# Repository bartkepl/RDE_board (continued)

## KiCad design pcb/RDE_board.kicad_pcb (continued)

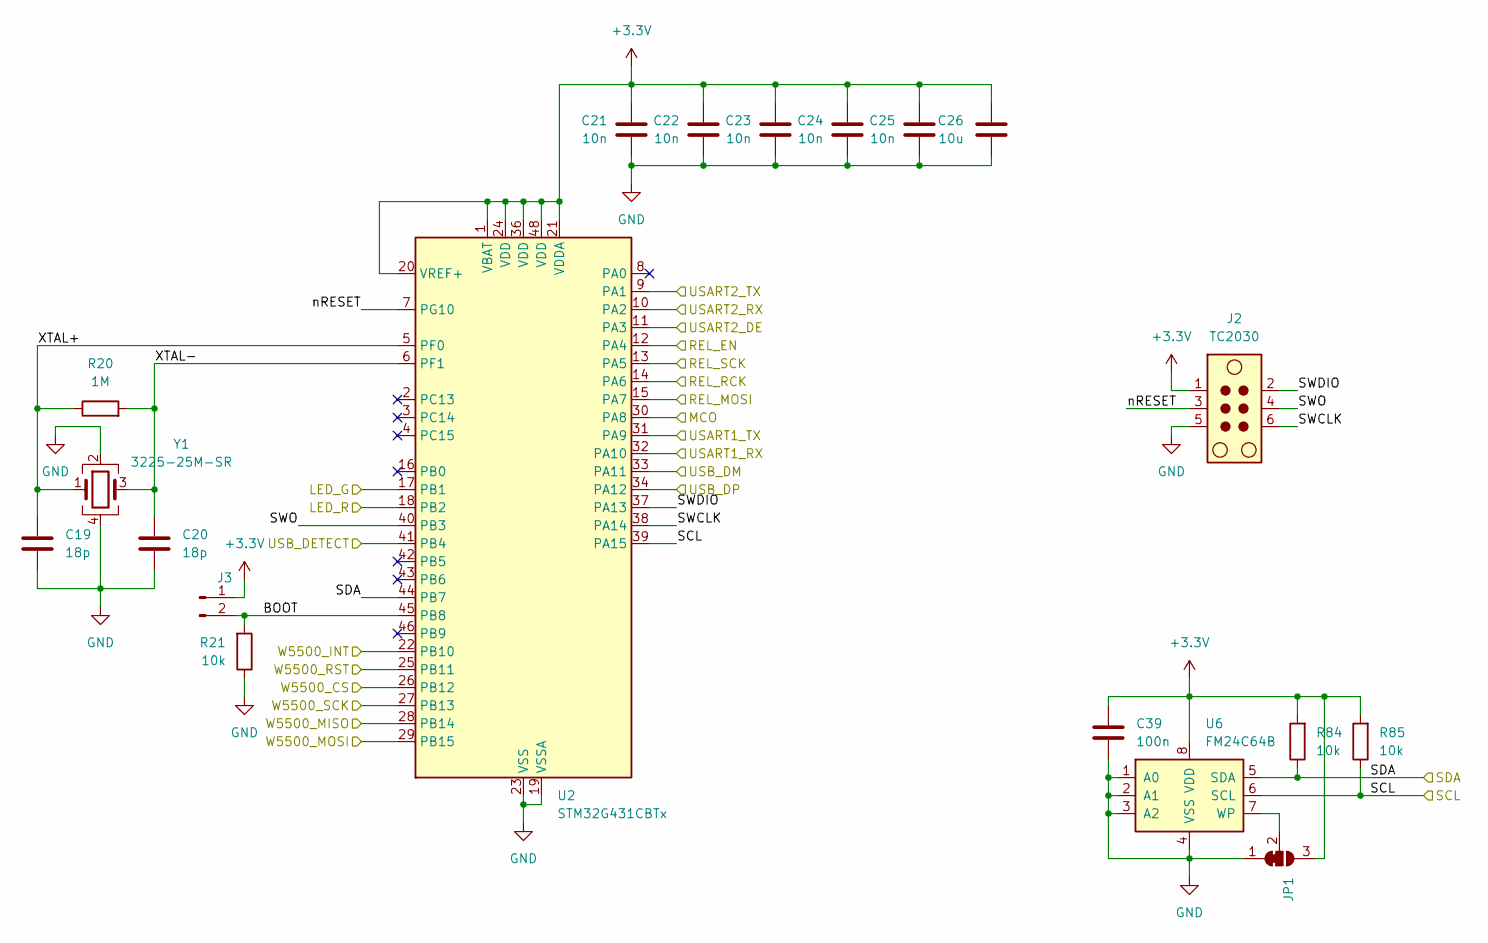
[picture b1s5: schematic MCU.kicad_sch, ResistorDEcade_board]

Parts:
C19, C20: 18p; C_0402_1005Metric_Pad0.74x0.62mm_HandSolder
C21, C22, C23, C24, C25: 10n; C_0603_1608Metric_Pad1.08x0.95mm_HandSolder
C26: 10u; C_1206_3216Metric_Pad1.33x1.80mm_HandSolder
C39: 100n; C_0603_1608Metric_Pad1.08x0.95mm_HandSolder
J2: TC2030; Tag-Connect_TC2030-IDC-NL_2x03_P1.27mm_Vertical
J3: Conn_01x02_Pin; PinHeader_1x02_P2.00mm_Vertical
JP1: SolderJumper_3_Bridged12; SolderJumper-3_P1.3mm_Bridged12_Pad1.0x1.5mm
R20: 1M; R_0402_1005Metric_Pad0.72x0.64mm_HandSolder
R21, R84, R85: 10k; R_0603_1608Metric_Pad0.98x0.95mm_HandSolder
U2: STM32G431CBTx; LQFP-48_7x7mm_P0.5mm
U6: FM24C64B; SOIC-8_3.9x4.9mm_P1.27mm
Y1: 3225-25M-SR; Crystal_SMD_3225-4Pin_3.2x2.5mm

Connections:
+3.3V: C21.2, C22.2, C23.2, C24.2, C25.2, C26.1, C39.1, J2.1, J3.1, JP1.3 (B), R84.2, R85.2, U2.1 (VBAT), U2.20 (VREF+), U2.21 (VDDA), U2.24 (VDD), U2.36 (VDD), U2.48 (VDD), U6.8 (VDD); also elsewhere on the board
/ConnectorDIN41612/DE: U2.11 (PA3); also elsewhere on the board
/ConnectorDIN41612/RxD: U2.10 (PA2); also elsewhere on the board
/ConnectorDIN41612/TxD: U2.9 (PA1); also elsewhere on the board
/ConnectorDIN41612/USART+: U2.31 (PA9); also elsewhere on the board
/ConnectorDIN41612/USART-: U2.32 (PA10); also elsewhere on the board
/ConnectorDIN41612/USB_D+: U2.34 (PA12); also elsewhere on the board
/ConnectorDIN41612/USB_D-: U2.33 (PA11); also elsewhere on the board
/ConnectorDIN41612/USB_DET: U2.41 (PB4); also elsewhere on the board
/EthernetPHY/CLKIN: U2.30 (PA8); also elsewhere on the board
/EthernetPHY/CS: U2.26 (PB12); also elsewhere on the board
/EthernetPHY/INT: U2.22 (PB10); also elsewhere on the board
/EthernetPHY/MISO: U2.28 (PB14); also elsewhere on the board
/EthernetPHY/MOSI: U2.29 (PB15); also elsewhere on the board
/EthernetPHY/RST: U2.25 (PB11); also elsewhere on the board
/EthernetPHY/SCK: U2.27 (PB13); also elsewhere on the board
/Frontend/RCK: U2.14 (PA6); also elsewhere on the board
/Frontend/REL_EN: U2.12 (PA4); also elsewhere on the board
/Frontend/SER_IN: U2.15 (PA7); also elsewhere on the board
/Frontend/SRCK: U2.13 (PA5); also elsewhere on the board
/MCU/BOOT: J3.2, R21.2, U2.45 (PB8)
/MCU/LED_G: U2.17 (PB1); also elsewhere on the board
/MCU/LED_R: U2.18 (PB2); also elsewhere on the board
/MCU/SCL: R85.1, U2.39 (PA15), U6.6 (SCL); also elsewhere on the board
/MCU/SDA: R84.1, U2.44 (PB7), U6.5 (SDA); also elsewhere on the board
/MCU/SWCLK: J2.6, U2.38 (PA14)
/MCU/SWDIO: J2.2, U2.37 (PA13)
/MCU/SWO: J2.4, U2.40 (PB3)
/MCU/XTAL+: C19.1, R20.1, U2.5 (PF0), Y1.1
/MCU/XTAL-: C20.1, R20.2, U2.6 (PF1), Y1.3
/MCU/nRESET: J2.3, U2.7 (PG10)
GND: C19.2, C20.2, C21.1, C22.1, C23.1, C24.1, C25.1, C26.2, C39.2, J2.5, JP1.1 (A), R21.1, U2.19 (VSSA), U2.23 (VSS), U2.35 (VSS), U2.47 (VSS), U6.1 (A0), U6.2 (A1), U6.3 (A2), U6.4 (VSS), Y1.2, Y1.4; also elsewhere on the board
unnamed: JP1.2 (C), U6.7 (WP)

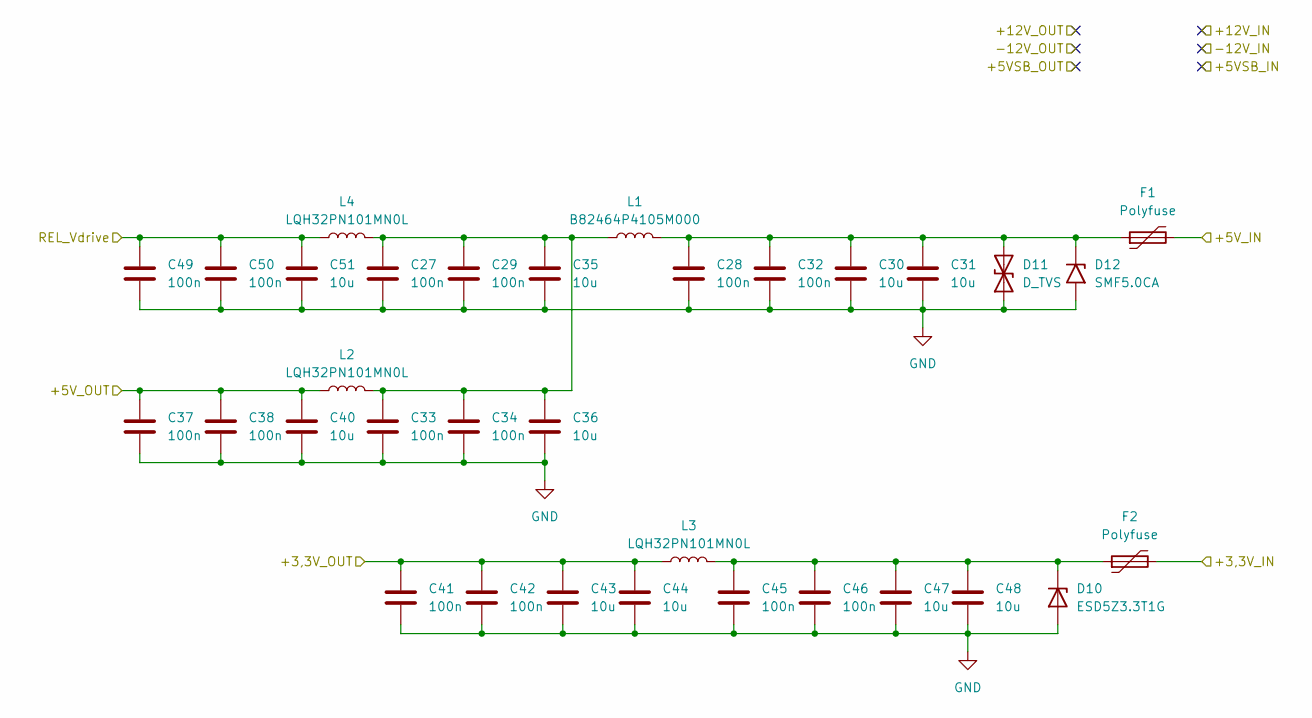
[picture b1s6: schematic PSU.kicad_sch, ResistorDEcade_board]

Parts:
C27, C28, C29, C32, C33, C34, C37, C38, C41, C42, C45, C46, C49, C50: 100n; C_0603_1608Metric_Pad1.08x0.95mm_HandSolder
C30, C31, C35, C36, C40, C43, C44, C47, C48, C51: 10u; C_1206_3216Metric_Pad1.33x1.80mm_HandSolder
D10: ESD5Z3.3T1G; D_SOD-523
D11: D_TVS; D_MiniMELF
D12: SMF5.0CA; D_SMF
F1, F2: Polyfuse; Fuse_1206_3216Metric_Pad1.42x1.75mm_HandSolder
L1: B82464P4105M000; L_10.4x10.4_H4.8
L2, L3, L4: LQH32PN101MN0L; L_1210_3225Metric

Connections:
+3.3V: C41.1, C42.1, C43.1, C44.1, L3.1; also elsewhere on the board
+5V: C37.1, C38.1, C40.1, L2.1; also elsewhere on the board
/ConnectorDIN41612/PSU/+3,3V_IN: F2.2; also elsewhere on the board
/ConnectorDIN41612/PSU/+5V_IN: F1.2; also elsewhere on the board
/ConnectorDIN41612/REL_Vdrive: C49.1, C50.1, C51.1, L4.1; also elsewhere on the board
GND: C27.2, C28.2, C29.2, C30.2, C31.2, C32.2, C33.2, C34.2, C35.2, C36.2, C37.2, C38.2, C40.2, C41.2, C42.2, C43.2, C44.2, C45.2, C46.2, C47.2, C48.2, C49.2, C50.2, C51.2, D10.2 (A), D11.1 (A1), D12.2 (A2); also elsewhere on the board
unnamed: C27.1, C29.1, C33.1, C34.1, C35.1, C36.1, L1.1, L2.2, L4.2
unnamed: C45.1, C46.1, C47.1, C48.1, D10.1 (K), F2.1, L3.2
unnamed: C28.1, C30.1, C31.1, C32.1, D11.2 (A2), D12.1 (A1), F1.1, L1.2

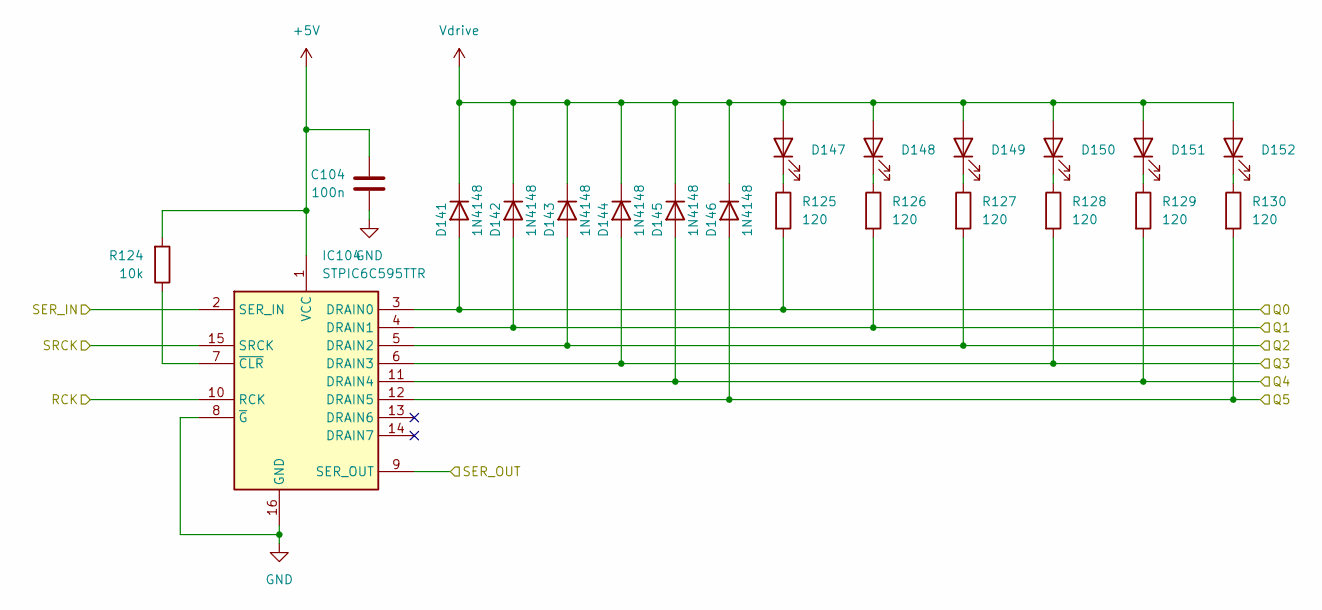
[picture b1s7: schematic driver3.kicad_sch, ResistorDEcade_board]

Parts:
C104: 100n; C_0603_1608Metric_Pad1.08x0.95mm_HandSolder
D141, D142, D143, D144, D145, D146: 1N4148; D_MiniMELF
D147, D148, D149, D150, D151, D152: LED_0603_1608Metric_Pad1.05x0.95mm_HandSolder
IC104: STPIC6C595TTR; SOP65P640X120-16N; Manufacturer_Part_Number STPIC6C595TTR
R124: 10k; R_0603_1608Metric_Pad0.98x0.95mm_HandSolder
R125, R126, R127, R128, R129, R130: 120; R_0603_1608Metric_Pad0.98x0.95mm_HandSolder

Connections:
+5V: C104.2, IC104.1 (VCC), R124.2; also elsewhere on the board
/Frontend/1x1k: D142.2 (A), IC104.4 (DRAIN1), R126.2; also elsewhere on the board
/Frontend/2x1k: D143.2 (A), IC104.5 (DRAIN2), R127.2; also elsewhere on the board
/Frontend/3x1k: D144.2 (A), IC104.6 (DRAIN3), R128.2; also elsewhere on the board
/Frontend/4x1k: D145.2 (A), IC104.11 (DRAIN4), R129.2; also elsewhere on the board
/Frontend/5x1k: D146.2 (A), IC104.12 (DRAIN5), R130.2; also elsewhere on the board
/Frontend/Driver2/SER_OUT: IC104.2 (SER_IN); also elsewhere on the board
/Frontend/Driver3/SER_OUT: IC104.9 (SER_OUT); also elsewhere on the board
/Frontend/RCK: IC104.10 (RCK); also elsewhere on the board
/Frontend/SHORTx1k: D141.2 (A), IC104.3 (DRAIN0), R125.2; also elsewhere on the board
/Frontend/SRCK: IC104.15 (SRCK); also elsewhere on the board
GND: C104.1, IC104.8 (~G), IC104.16 (GND); also elsewhere on the board
unnamed: D147.1 (K), R125.1
unnamed: D148.1 (K), R126.1
unnamed: D149.1 (K), R127.1
unnamed: D150.1 (K), R128.1
unnamed: D151.1 (K), R129.1
unnamed: D152.1 (K), R130.1
unnamed: IC104.7 (~CLR), R124.1
Vdrive: D141.1 (K), D142.1 (K), D143.1 (K), D144.1 (K), D145.1 (K), D146.1 (K), D147.2 (A), D148.2 (A), D149.2 (A), D150.2 (A), D151.2 (A), D152.2 (A); also elsewhere on the board

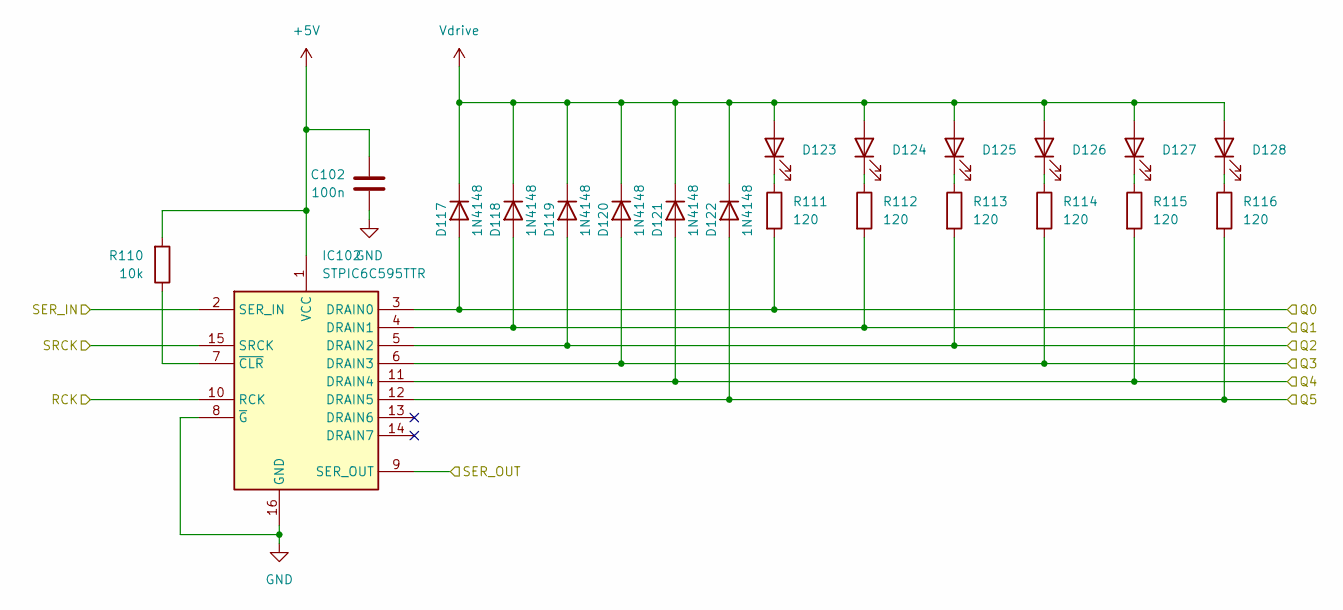
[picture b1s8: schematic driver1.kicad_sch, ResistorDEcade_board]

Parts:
C102: 100n; C_0603_1608Metric_Pad1.08x0.95mm_HandSolder
D117, D118, D119, D120, D121, D122: 1N4148; D_MiniMELF
D123, D124, D125, D126, D127, D128: LED_0603_1608Metric_Pad1.05x0.95mm_HandSolder
IC102: STPIC6C595TTR; SOP65P640X120-16N; Manufacturer_Part_Number STPIC6C595TTR
R110: 10k; R_0603_1608Metric_Pad0.98x0.95mm_HandSolder
R111, R112, R113, R114, R115, R116: 120; R_0603_1608Metric_Pad0.98x0.95mm_HandSolder

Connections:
+5V: C102.2, IC102.1 (VCC), R110.2; also elsewhere on the board
/Frontend/1x10: D118.2 (A), IC102.4 (DRAIN1), R112.2; also elsewhere on the board
/Frontend/2x10: D119.2 (A), IC102.5 (DRAIN2), R113.2; also elsewhere on the board
/Frontend/3x10: D120.2 (A), IC102.6 (DRAIN3), R114.2; also elsewhere on the board
/Frontend/4x10: D121.2 (A), IC102.11 (DRAIN4), R115.2; also elsewhere on the board
/Frontend/5x10: D122.2 (A), IC102.12 (DRAIN5), R116.2; also elsewhere on the board
/Frontend/Driver1/SER_OUT: IC102.9 (SER_OUT); also elsewhere on the board
/Frontend/Driver/SER_OUT: IC102.2 (SER_IN); also elsewhere on the board
/Frontend/RCK: IC102.10 (RCK); also elsewhere on the board
/Frontend/SHORTx10: D117.2 (A), IC102.3 (DRAIN0), R111.2; also elsewhere on the board
/Frontend/SRCK: IC102.15 (SRCK); also elsewhere on the board
GND: C102.1, IC102.8 (~G), IC102.16 (GND); also elsewhere on the board
unnamed: D123.1 (K), R111.1
unnamed: D124.1 (K), R112.1
unnamed: D125.1 (K), R113.1
unnamed: D126.1 (K), R114.1
unnamed: D127.1 (K), R115.1
unnamed: D128.1 (K), R116.1
unnamed: IC102.7 (~CLR), R110.1
Vdrive: D117.1 (K), D118.1 (K), D119.1 (K), D120.1 (K), D121.1 (K), D122.1 (K), D123.2 (A), D124.2 (A), D125.2 (A), D126.2 (A), D127.2 (A), D128.2 (A); also elsewhere on the board

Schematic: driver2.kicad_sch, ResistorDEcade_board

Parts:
C103: 100n; C_0603_1608Metric_Pad1.08x0.95mm_HandSolder
D129, D130, D131, D132, D133, D134: 1N4148; D_MiniMELF
D135, D136, D137, D138, D139, D140: LED_0603_1608Metric_Pad1.05x0.95mm_HandSolder
IC103: STPIC6C595TTR; SOP65P640X120-16N; Manufacturer_Part_Number STPIC6C595TTR
R117: 10k; R_0603_1608Metric_Pad0.98x0.95mm_HandSolder
R118, R119, R120, R121, R122, R123: 120; R_0603_1608Metric_Pad0.98x0.95mm_HandSolder

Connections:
+5V: C103.2, IC103.1 (VCC), R117.2; also elsewhere on the board
/Frontend/1x100: D130.2 (A), IC103.4 (DRAIN1), R119.2; also elsewhere on the board
/Frontend/2x100: D131.2 (A), IC103.5 (DRAIN2), R120.2; also elsewhere on the board
/Frontend/3x100: D132.2 (A), IC103.6 (DRAIN3), R121.2; also elsewhere on the board
/Frontend/4x100: D133.2 (A), IC103.11 (DRAIN4), R122.2; also elsewhere on the board
/Frontend/5x100: D134.2 (A), IC103.12 (DRAIN5), R123.2; also elsewhere on the board
/Frontend/Driver1/SER_OUT: IC103.2 (SER_IN); also elsewhere on the board
/Frontend/Driver2/SER_OUT: IC103.9 (SER_OUT); also elsewhere on the board
/Frontend/RCK: IC103.10 (RCK); also elsewhere on the board
/Frontend/SHORTx100: D129.2 (A), IC103.3 (DRAIN0), R118.2; also elsewhere on the board
/Frontend/SRCK: IC103.15 (SRCK); also elsewhere on the board
GND: C103.1, IC103.8 (~G), IC103.16 (GND); also elsewhere on the board
unnamed: D135.1 (K), R118.1
unnamed: D136.1 (K), R119.1
unnamed: D137.1 (K), R120.1
unnamed: D138.1 (K), R121.1
unnamed: D139.1 (K), R122.1
unnamed: D140.1 (K), R123.1
unnamed: IC103.7 (~CLR), R117.1
Vdrive: D129.1 (K), D130.1 (K), D131.1 (K), D132.1 (K), D133.1 (K), D134.1 (K), D135.2 (A), D136.2 (A), D137.2 (A), D138.2 (A), D139.2 (A), D140.2 (A); also elsewhere on the board

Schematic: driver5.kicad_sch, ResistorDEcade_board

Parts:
C106: 100n; C_0603_1608Metric_Pad1.08x0.95mm_HandSolder
D165, D166, D167, D168, D169, D170: 1N4148; D_MiniMELF
D171, D172, D173, D174, D175, D176: LED_0603_1608Metric_Pad1.05x0.95mm_HandSolder
IC106: STPIC6C595TTR; SOP65P640X120-16N; Manufacturer_Part_Number STPIC6C595TTR
R138: 10k; R_0603_1608Metric_Pad0.98x0.95mm_HandSolder
R139, R140, R141, R142, R143, R144: 120; R_0603_1608Metric_Pad0.98x0.95mm_HandSolder

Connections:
+5V: C106.2, IC106.1 (VCC), R138.2; also elsewhere on the board
/Frontend/1x100k: D166.2 (A), IC106.4 (DRAIN1), R140.2; also elsewhere on the board
/Frontend/2x100k: D167.2 (A), IC106.5 (DRAIN2), R141.2; also elsewhere on the board
/Frontend/3x100k: D168.2 (A), IC106.6 (DRAIN3), R142.2; also elsewhere on the board
/Frontend/4x100k: D169.2 (A), IC106.11 (DRAIN4), R143.2; also elsewhere on the board
/Frontend/5x100k: D170.2 (A), IC106.12 (DRAIN5), R144.2; also elsewhere on the board
/Frontend/Driver4/SER_OUT: IC106.2 (SER_IN); also elsewhere on the board
/Frontend/Driver5/SER_OUT: IC106.9 (SER_OUT)
/Frontend/RCK: IC106.10 (RCK); also elsewhere on the board
/Frontend/SHORTx100k: D165.2 (A), IC106.3 (DRAIN0), R139.2; also elsewhere on the board
/Frontend/SRCK: IC106.15 (SRCK); also elsewhere on the board
GND: C106.1, IC106.8 (~G), IC106.16 (GND); also elsewhere on the board
unnamed: D171.1 (K), R139.1
unnamed: D172.1 (K), R140.1
unnamed: D173.1 (K), R141.1
unnamed: D174.1 (K), R142.1
unnamed: D175.1 (K), R143.1
unnamed: D176.1 (K), R144.1
unnamed: IC106.7 (~CLR), R138.1
Vdrive: D165.1 (K), D166.1 (K), D167.1 (K), D168.1 (K), D169.1 (K), D170.1 (K), D171.2 (A), D172.2 (A), D173.2 (A), D174.2 (A), D175.2 (A), D176.2 (A); also elsewhere on the board

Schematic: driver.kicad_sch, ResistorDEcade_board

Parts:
C101: 100n; C_0603_1608Metric_Pad1.08x0.95mm_HandSolder
D101, D102, D103, D104, D105, D106, D107, D108: 1N4148; D_MiniMELF
D109, D110, D111, D112, D113, D114, D115, D116: LED_0603_1608Metric_Pad1.05x0.95mm_HandSolder
IC101: STPIC6C595TTR; SOP65P640X120-16N; Manufacturer_Part_Number STPIC6C595TTR
R101: 10k; R_0603_1608Metric_Pad0.98x0.95mm_HandSolder
R102, R103, R104, R105, R106, R107, R108, R109: 120; R_0603_1608Metric_Pad0.98x0.95mm_HandSolder

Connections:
+5V: C101.2, IC101.1 (VCC), R101.2; also elsewhere on the board
/Frontend/1x1: D102.2 (A), IC101.4 (DRAIN1), R103.2; also elsewhere on the board
/Frontend/2x1: D103.2 (A), IC101.5 (DRAIN2), R104.2; also elsewhere on the board
/Frontend/3x1: D104.2 (A), IC101.6 (DRAIN3), R105.2; also elsewhere on the board
/Frontend/4x1: D105.2 (A), IC101.11 (DRAIN4), R106.2; also elsewhere on the board
/Frontend/5x1: D106.2 (A), IC101.12 (DRAIN5), R107.2; also elsewhere on the board
/Frontend/Driver/SER_OUT: IC101.9 (SER_OUT); also elsewhere on the board
/Frontend/FRONT: D107.2 (A), IC101.13 (DRAIN6), R108.2; also elsewhere on the board
/Frontend/RCK: IC101.10 (RCK); also elsewhere on the board
/Frontend/SER_IN: IC101.2 (SER_IN); also elsewhere on the board
/Frontend/SHORT: D108.2 (A), IC101.14 (DRAIN7), R109.2; also elsewhere on the board
/Frontend/SHORTx1: D101.2 (A), IC101.3 (DRAIN0), R102.2; also elsewhere on the board
/Frontend/SRCK: IC101.15 (SRCK); also elsewhere on the board
GND: C101.1, IC101.8 (~G), IC101.16 (GND); also elsewhere on the board
unnamed: D109.1 (K), R102.1
unnamed: D110.1 (K), R103.1
unnamed: D111.1 (K), R104.1
unnamed: D112.1 (K), R105.1
unnamed: D113.1 (K), R106.1
unnamed: D114.1 (K), R107.1
unnamed: D115.1 (K), R108.1
unnamed: D116.1 (K), R109.1
unnamed: IC101.7 (~CLR), R101.1
Vdrive: D101.1 (K), D102.1 (K), D103.1 (K), D104.1 (K), D105.1 (K), D106.1 (K), D107.1 (K), D108.1 (K), D109.2 (A), D110.2 (A), D111.2 (A), D112.2 (A), D113.2 (A), D114.2 (A), D115.2 (A), D116.2 (A); also elsewhere on the board

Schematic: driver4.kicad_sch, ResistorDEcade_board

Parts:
C105: 100n; C_0603_1608Metric_Pad1.08x0.95mm_HandSolder
D153, D154, D155, D156, D157, D158: 1N4148; D_MiniMELF
D159, D160, D161, D162, D163, D164: LED_0603_1608Metric_Pad1.05x0.95mm_HandSolder
IC105: STPIC6C595TTR; SOP65P640X120-16N; Manufacturer_Part_Number STPIC6C595TTR
R131: 10k; R_0603_1608Metric_Pad0.98x0.95mm_HandSolder
R132, R133, R134, R135, R136, R137: 120; R_0603_1608Metric_Pad0.98x0.95mm_HandSolder

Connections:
+5V: C105.2, IC105.1 (VCC), R131.2; also elsewhere on the board
/Frontend/1x10k: D154.2 (A), IC105.4 (DRAIN1), R133.2; also elsewhere on the board
/Frontend/2x10k: D155.2 (A), IC105.5 (DRAIN2), R134.2; also elsewhere on the board
/Frontend/3x10k: D156.2 (A), IC105.6 (DRAIN3), R135.2; also elsewhere on the board
/Frontend/4x10k: D157.2 (A), IC105.11 (DRAIN4), R136.2; also elsewhere on the board
/Frontend/5x10k: D158.2 (A), IC105.12 (DRAIN5), R137.2; also elsewhere on the board
/Frontend/Driver3/SER_OUT: IC105.2 (SER_IN); also elsewhere on the board
/Frontend/Driver4/SER_OUT: IC105.9 (SER_OUT); also elsewhere on the board
/Frontend/RCK: IC105.10 (RCK); also elsewhere on the board
/Frontend/SHORTx10k: D153.2 (A), IC105.3 (DRAIN0), R132.2; also elsewhere on the board
/Frontend/SRCK: IC105.15 (SRCK); also elsewhere on the board
GND: C105.1, IC105.8 (~G), IC105.16 (GND); also elsewhere on the board
unnamed: D159.1 (K), R132.1
unnamed: D160.1 (K), R133.1
unnamed: D161.1 (K), R134.1
unnamed: D162.1 (K), R135.1
unnamed: D163.1 (K), R136.1
unnamed: D164.1 (K), R137.1
unnamed: IC105.7 (~CLR), R131.1
Vdrive: D153.1 (K), D154.1 (K), D155.1 (K), D156.1 (K), D157.1 (K), D158.1 (K), D159.2 (A), D160.2 (A), D161.2 (A), D162.2 (A), D163.2 (A), D164.2 (A); also elsewhere on the board

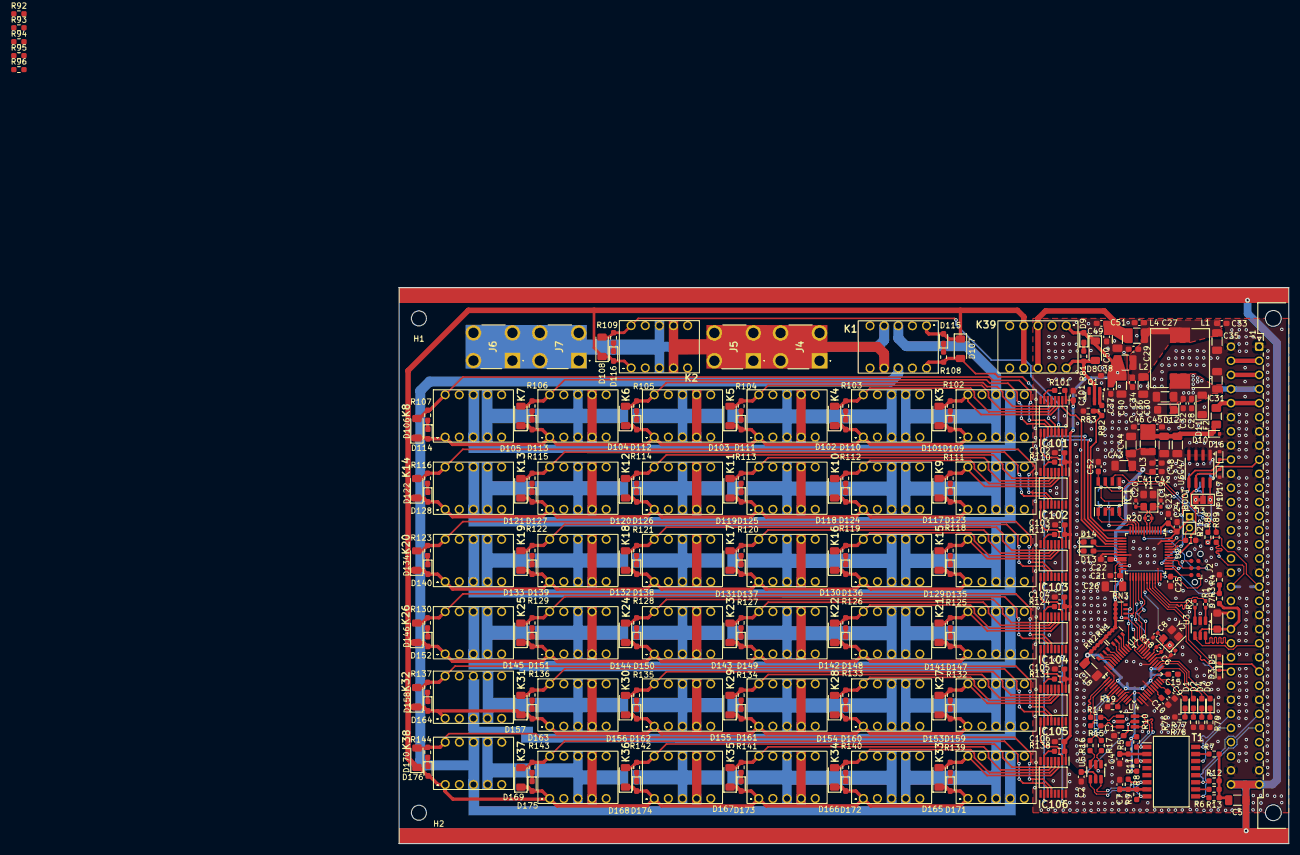
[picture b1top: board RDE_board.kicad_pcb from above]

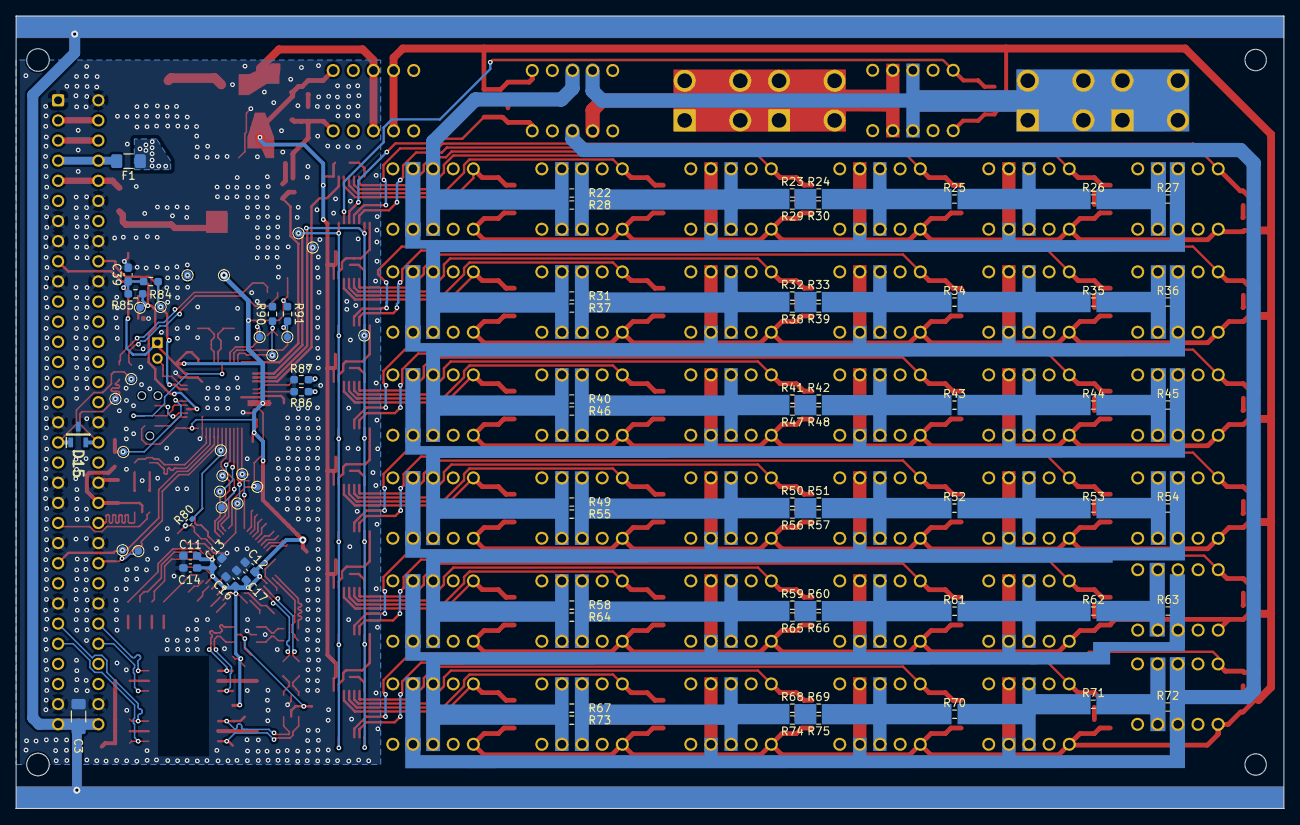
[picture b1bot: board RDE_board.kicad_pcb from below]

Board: 2 copper layers, 160.0 x 100.0 mm, 388 parts (93 on the bottom side), 230 nets.

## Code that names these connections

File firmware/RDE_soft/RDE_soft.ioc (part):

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Mcu.Name=STM32G431C(6-8-B)Tx
Mcu.Package=LQFP48
Mcu.UserName=STM32G431CBTx
PA1.Mode=Hardware Flow Control (RS485)
PA1.Signal=USART2_DE
PA10.Mode=Asynchronous
PA10.Signal=USART1_RX
PA11.Mode=Device
PA11.Signal=USB_DM
PA12.Mode=Device
PA12.Signal=USB_DP
PA13.Mode=Trace_Asynchronous_SW
PA13.Signal=SYS_JTMS-SWDIO
PA14.Mode=Trace_Asynchronous_SW
PA14.Signal=SYS_JTCK-SWCLK
PA15.GPIOParameters=GPIO_Speed
PA15.GPIO_Speed=GPIO_SPEED_FREQ_MEDIUM
PA15.Mode=I2C
PA15.Signal=I2C1_SCL
PA2.Mode=Asynchronous
PA2.Signal=USART2_TX
PA3.Mode=Asynchronous
PA3.Signal=USART2_RX
PA4.GPIOParameters=GPIO_Label
PA4.GPIO_Label=REL_EN
PA4.Signal=GPIO_Output
PA5.GPIOParameters=GPIO_Speed,GPIO_Label
PA5.GPIO_Label=REL_SCK
PA5.GPIO_Speed=GPIO_SPEED_FREQ_HIGH
PA5.Mode=TX_Only_Simplex_Unidirect_Master
PA5.Signal=SPI1_SCK
PA6.GPIOParameters=GPIO_Label
PA6.GPIO_Label=REL_RCK
PA6.Signal=GPIO_Output
PA7.GPIOParameters=GPIO_Speed,GPIO_Label
PA7.GPIO_Label=REL_MOSI
PA7.GPIO_Speed=GPIO_SPEED_FREQ_HIGH
PA7.Mode=TX_Only_Simplex_Unidirect_Master
PA7.Signal=SPI1_MOSI
PA8.GPIOParameters=GPIO_Speed,GPIO_Label
PA8.GPIO_Label=W5500_CLK
PA8.GPIO_Speed=GPIO_SPEED_FREQ_VERY_HIGH
PA8.Mode=Clock-out
PA8.Signal=RCC_MCO
PA9.Mode=Asynchronous
PA9.Signal=USART1_TX
PB1.GPIOParameters=GPIO_Label
PB1.GPIO_Label=LED_G
PB1.Signal=GPIO_Output
PB10.GPIOParameters=GPIO_Label
PB10.GPIO_Label=W5500_INT
PB10.Signal=GPIO_Input
PB11.GPIOParameters=GPIO_Label
PB11.GPIO_Label=W5500_RST
PB11.Signal=GPIO_Output
PB12.GPIOParameters=GPIO_Label
PB12.GPIO_Label=W5500_CS
PB12.Signal=GPIO_Output
PB13.GPIOParameters=GPIO_Speed,GPIO_Label
PB13.GPIO_Label=W5500_SCK
PB13.GPIO_Speed=GPIO_SPEED_FREQ_VERY_HIGH
PB13.Mode=Full_Duplex_Master
PB13.Signal=SPI2_SCK
PB14.GPIOParameters=GPIO_Speed,GPIO_Label
PB14.GPIO_Label=W5500_MISO
PB14.GPIO_Speed=GPIO_SPEED_FREQ_VERY_HIGH
PB14.Mode=Full_Duplex_Master
PB14.Signal=SPI2_MISO
PB15.GPIOParameters=GPIO_Speed,GPIO_Label
PB15.GPIO_Label=W5500_MOSI
PB15.GPIO_Speed=GPIO_SPEED_FREQ_VERY_HIGH
PB15.Mode=Full_Duplex_Master
PB15.Signal=SPI2_MOSI
PB2.GPIOParameters=GPIO_Label
PB2.GPIO_Label=LED_R
PB2.Signal=GPIO_Output
PB3.Mode=Trace_Asynchronous_SW
PB3.Signal=SYS_JTDO-SWO
PB4.GPIOParameters=GPIO_Label
PB4.GPIO_Label=USB_DETECT
PB4.Signal=GPIO_Input
PB7.GPIOParameters=GPIO_Speed
PB7.GPIO_Speed=GPIO_SPEED_FREQ_MEDIUM
PB7.Mode=I2C
PB7.Signal=I2C1_SDA
PF0-OSC_IN.Mode=HSE-External-Oscillator
PF0-OSC_IN.Signal=RCC_OSC_IN
PF1-OSC_OUT.Mode=HSE-External-Oscillator
PF1-OSC_OUT.Signal=RCC_OSC_OUT
RCC.HSE_VALUE=25000000
RCC.SYSCLKFreq_VALUE=125000000
RCC.SYSCLKSource=RCC_SYSCLKSOURCE_PLLCLK
board=custom

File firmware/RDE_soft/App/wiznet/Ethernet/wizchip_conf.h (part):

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#define PHY_CONFBY_SW            1     ///< Configured PHY operation mode by SW register   
#define PHY_MODE_MANUAL          0     ///< Configured PHY operation mode with user setting.
#define PHY_MODE_AUTONEGO        1     ///< Configured PHY operation mode with auto-negotiation
#define PHY_SPEED_10             0     ///< Link Speed 10
#define PHY_SPEED_100            1     ///< Link Speed 100
#define PHY_DUPLEX_HALF          0     ///< Link Half-Duplex
#define PHY_DUPLEX_FULL          1     ///< Link Full-Duplex
#define PHY_LINK_OFF             0     ///< Link Off
#define PHY_LINK_ON              1     ///< Link On
#define PHY_POWER_NORM           0     ///< PHY power normal mode
#define PHY_POWER_DOWN           1     ///< PHY power down mode 

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
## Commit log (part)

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2026-02-11 First sch and pcb revision, README and LICENSE update.
2026-02-12 Added CSV bom
2026-02-14 Added i2c for backplane config, testpoints. File organization
2026-02-18 Modified file organization, added jobsets, pcb sch cleaning
2026-02-21 Little cleaning
2026-02-21 Updated revision: v0.3
2026-02-21 First production
2026-03-10 Edited Resistor array to be included in bom
2026-05-09 Firmware development. USBTMC done, ETH almost with hardware and soft modifications. By claude
2026-05-10 Done core functionality by claude. Needs polishing
2026-05-10 Added FRAM param storage and calibration by claude
2026-05-15 More development
2026-05-15 Little polishing
2026-05-24 Add NET:PHY:MODE SCPI, WIZnet OUI MAC, improved autocal and PDF report
    Firmware:
    - NET:PHY:MODE 0/1/2 (AUTO/10M-HD/100M-FD) configurable via SCPI, stored in FRAM
    - MAC address uses WIZnet OUI prefix (00:08:DC) instead of locally-administered
    - net_config_t: added phy_mode field, renamed mask→sn, magic updated
    - FRAM address map compacted (removed padding between cal_data and cal_config)
    - New SYSTem:FRAM:DIAG? and SYSTem:I2C:SCAN? SCPI commands for diagnostics
